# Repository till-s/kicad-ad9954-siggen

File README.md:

# Simple 1Hz-100MHz Signal Generator with AD9954

This project implements a simple sine-wave generator from a few Hz
to ~100MHz. The Reference/sampling frequency is 400MHz.
The output is buffered by a OP859 amplifier which does level-shifting,
and differential to single-ended conversion.

An analog LPF at the output supresses higher harmonics and provides
the DC-coupled signal into a 50 Ohm load (i.e., the filter was
designed for a 50Ohm termination). The ripple over the frequency range
is in the order of 1dB.

The output amplitude can be (digitally) scaled from ~1Vp (0.7V RMS) down
to 0Vp.

The AD9954 is programmed via USB (USB-SPI converter) by a simple python
software (in the sw/ subdirectory). Power is supplied by USB as well.

The assembled PCB fits into a Hammond 1455D601 extruded aluminum box
(60mm x 42.5mm x 23mm).

The PCB requires 4 layers.

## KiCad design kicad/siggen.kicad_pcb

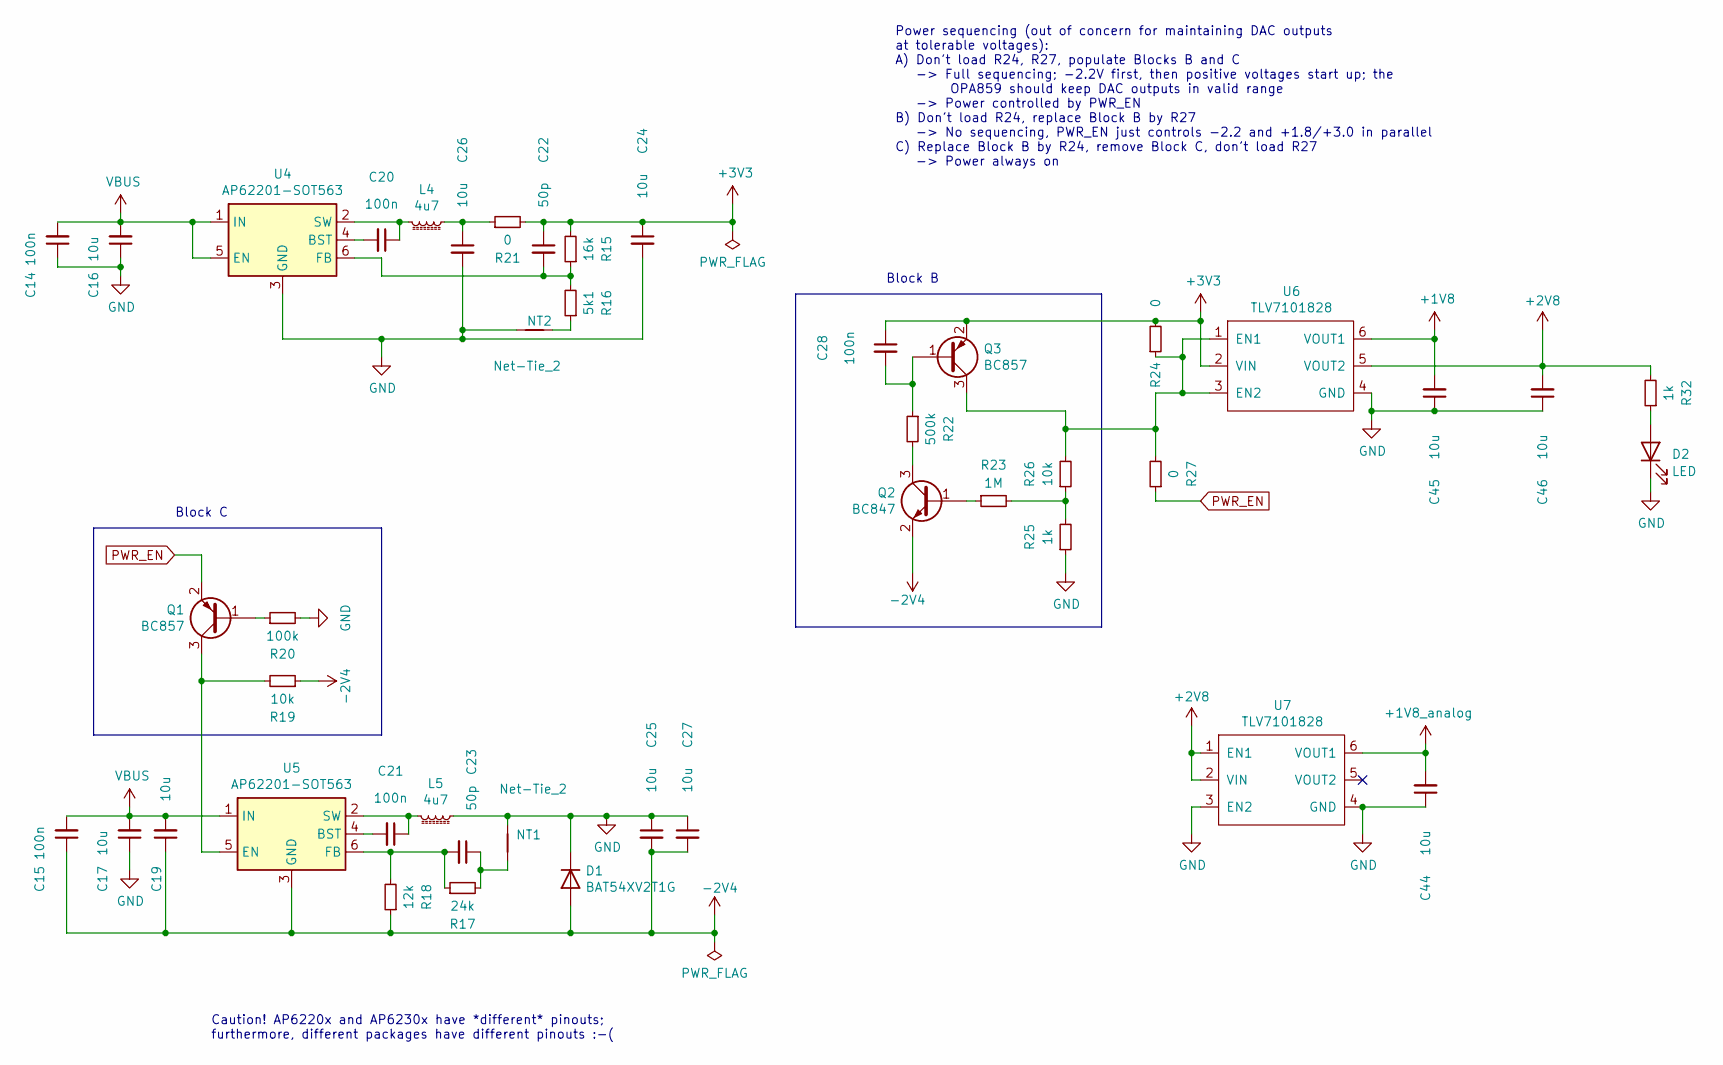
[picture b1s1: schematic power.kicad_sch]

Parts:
C14, C15, C20, C21, C28: 100n; C_0603_1608Metric
C16, C17, C19, C24, C25, C26, C27, C44, C45, C46: 10u; C_1206_3216Metric
C22, C23: 50p; C_0603_1608Metric
D1: BAT54XV2T1G; D_SOD-523
D2: LED; LED_0603_1608Metric
L4, L5: 4u7; L_Taiyo-Yuden_NR-50xx
NT1, NT2: Net-Tie_2; NetTie-2_SMD_Pad0.5mm
Q1, Q3: BC857; SOT-23
Q2: BC847; SOT-23
R15: 16k; R_0603_1608Metric
R16: 5k1; R_0603_1608Metric
R17: 24k; R_0603_1608Metric
R18: 12k; R_0603_1608Metric
R19, R26: 10k; R_0603_1608Metric
R20: 100k; R_0603_1608Metric
R21, R24, R27: 0; R_0603_1608Metric
R22: 500k; R_0603_1608Metric
R23: 1M; R_0603_1608Metric
R25, R32: 1k; R_0603_1608Metric
U4, U5: AP62201-SOT563; SOT-563-adjusted
U6, U7: TLV7101828; WSON-6_1.5x1.5mm_P0.5mm

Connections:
+1V8: C45.2, U6.6 (VOUT1); also elsewhere on the board
+1V8_analog: C44.2, U7.6 (VOUT1); also elsewhere on the board
+2V8: C46.2, R32.2, U6.5 (VOUT2), U7.1 (EN1), U7.2 (VIN); also elsewhere on the board
+3V3: C22.1, C24.1, C28.1, Q3.2 (E), R15.2, R21.2, R24.2, U6.2 (VIN); also elsewhere on the board
-2V4: C15.1, C19.1, C25.2, C27.2, D1.2 (A), Q2.2 (E), R18.1, R19.1, U5.3 (GND); also elsewhere on the board
GND: C14.1, C16.1, C17.1, C24.2, C25.1, C26.2, C27.1, C44.1, C45.1, C46.1, D1.1 (K), D2.1 (K), L5.1, NT1.1, NT2.2, R20.2, R25.1, U4.3 (GND), U6.4 (GND), U7.3 (EN2), U7.4 (GND); also elsewhere on the board
unnamed: C23.1, NT1.2, R17.2
unnamed: C26.1, L4.1, R21.1
unnamed: D2.2 (A), R32.1
unnamed: NT2.1, R16.1
unnamed: Q1.1 (B), R20.1
unnamed: Q1.3 (C), R19.2, U5.5 (EN)
unnamed: Q2.1 (B), R23.1
unnamed: Q2.3 (C), R22.2
unnamed: C28.2, Q3.1 (B), R22.1
unnamed: Q3.3 (C), R24.1, R26.2, R27.2, U6.1 (EN1), U6.3 (EN2)
unnamed: R23.2, R25.2, R26.1
unnamed: C20.2, U4.4 (BST)
unnamed: C22.2, R15.1, R16.2, U4.6 (FB)
unnamed: C20.1, L4.2, U4.2 (SW)
unnamed: C21.2, U5.4 (BST)
unnamed: C23.2, R17.1, R18.2, U5.6 (FB)
unnamed: C21.1, L5.2, U5.2 (SW)
PWR_EN: Q1.2 (E), R27.1; also elsewhere on the board
VBUS: C14.2, C15.2, C16.2, C17.2, C19.2, U4.1 (IN), U4.5 (EN), U5.1 (IN); also elsewhere on the board

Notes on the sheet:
Block B
Power sequencing (out of concern for maintaining DAC outputs at tolerable voltages): A) Don't load R24, R27, populate Blocks B and C -> Full sequencing; -2.2V first, then positive voltages start up; the OPA859 should keep DAC outputs in valid range -> Power controlled by PWR_EN B) Don't load R24, r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
Block C
Caution! AP6220x and AP6230x have *different* pinouts; furthermore, different packages have different pinouts :-(

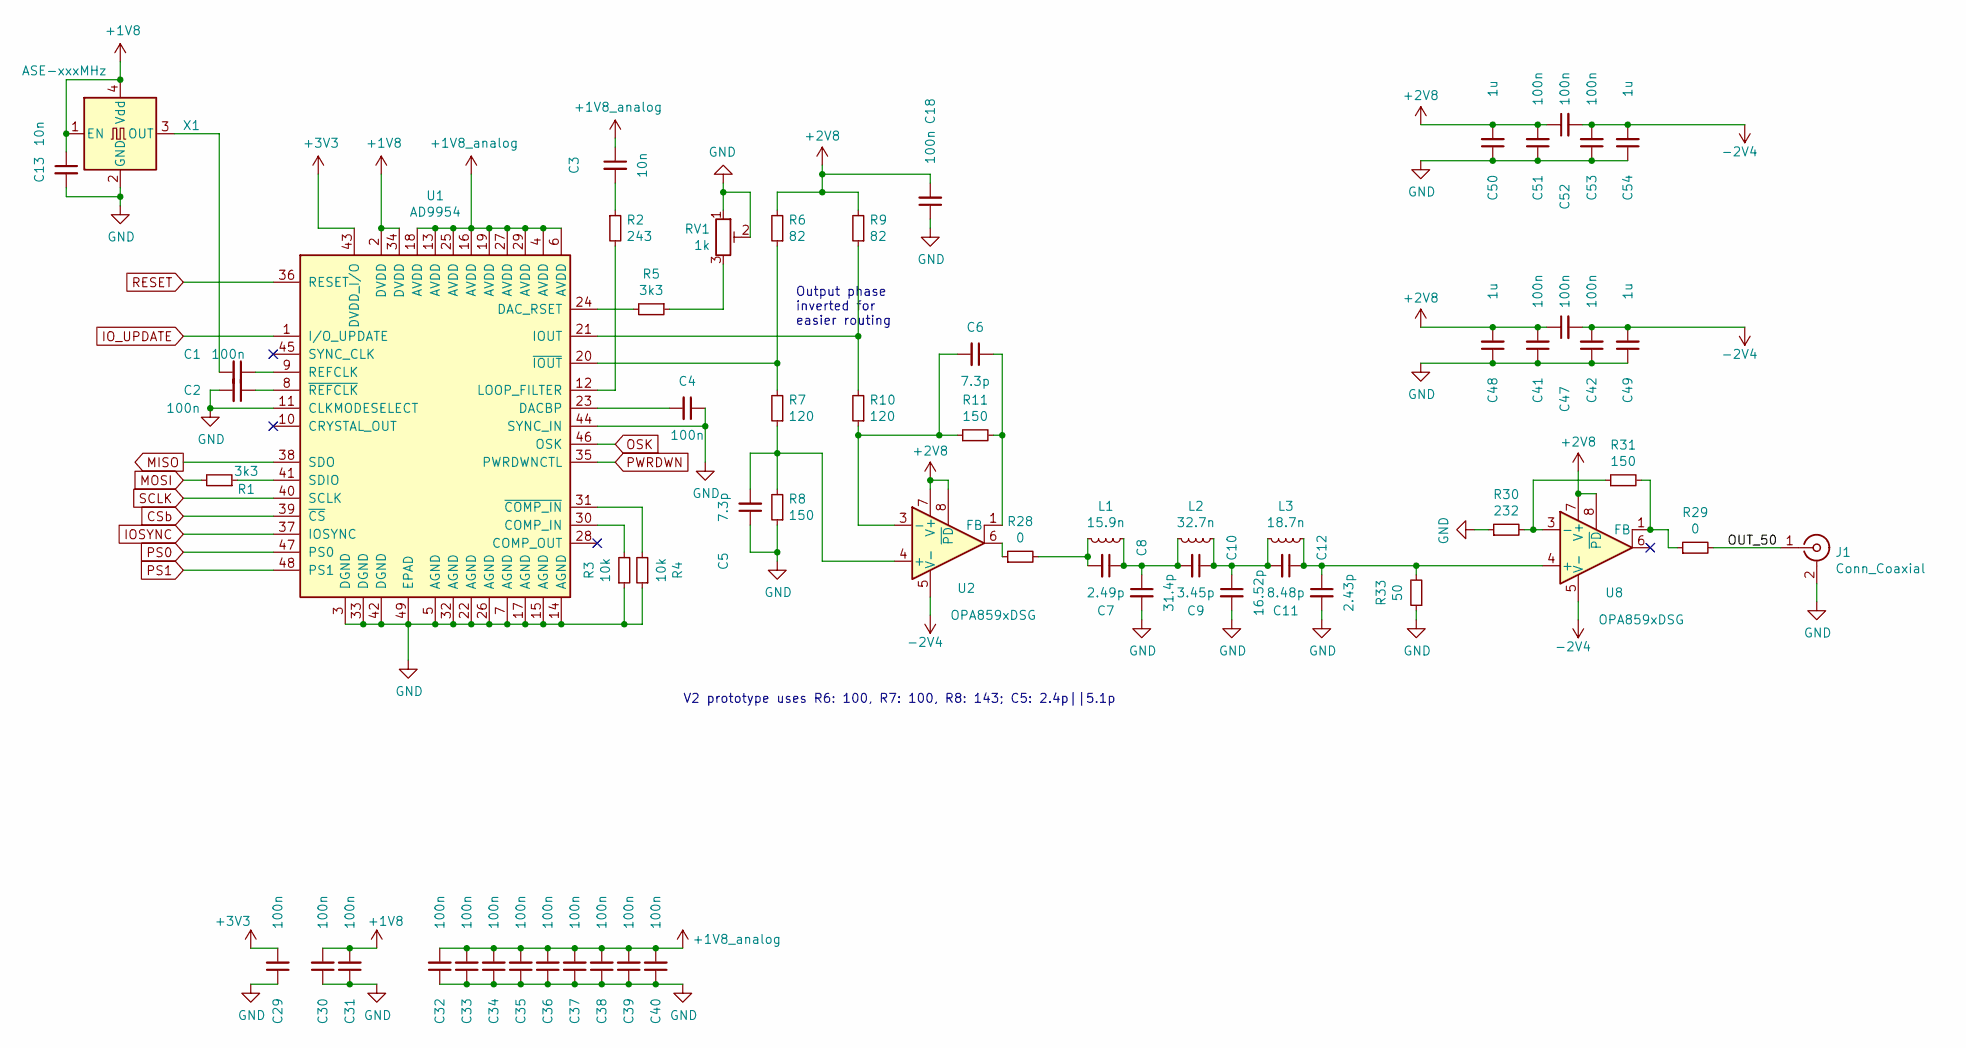
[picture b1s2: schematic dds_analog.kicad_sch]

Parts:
C1, C2: 100n; C_0603_1608Metric
C3, C13: 10n; C_0603_1608Metric
C4, C18, C29, C30, C31, C32, C33, C34, C35, C36, C37, C38, C39, C40, C41, C42, C47, C51, C52, C53: 100n; C_0402_1005Metric
C5, C6: 7.3p; C_0402_1005Metric
C7: 2.49p; C_0402_1005Metric
C8: 31.4p; C_0603_1608Metric
C9: 3.45p; C_0402_1005Metric
C10: 16.52p; C_0402_1005Metric
C11: 8.48p; C_0402_1005Metric
C12: 2.43p; C_0402_1005Metric
C48, C49, C50, C54: 1u; C_0805_2012Metric
J1: Conn_Coaxial; BNC_Molex_0731713150
L1: 15.9n; L_0603_1608Metric
L2: 32.7n; L_0603_1608Metric
L3: 18.7n; L_0603_1608Metric
R1, R5: 3k3; R_0603_1608Metric
R2: 243; R_0603_1608Metric
R3, R4: 10k; R_0603_1608Metric
R6, R9: 82; R_0402_1005Metric
R7, R10: 120; R_0402_1005Metric
R8, R11, R31: 150; R_0402_1005Metric
R28, R29: 0; R_0402_1005Metric
R30: 232; R_0402_1005Metric
R33: 50; R_0402_1005Metric
RV1: 1k; Bourns_PVG5A_Trimmer
U1: AD9954; TQFP-48-1EP_7x7mm_P0.5mm_EP3.5x3.5mm
U2, U8: OPA859xDSG; WSON-8-1EP_2x2mm_P0.5mm_EP0.9x1.6mm
X1: ASE-xxxMHz; Oscillator_SMD_Abracon_ASE-4Pin_3.2x2.5mm

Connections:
+1V8: C13.1, C30.2, C31.2, U1.2 (DVDD), U1.34 (DVDD), X1.1 (EN), X1.4 (Vdd); also elsewhere on the board
+1V8_analog: C3.1, C32.2, C33.2, C34.2, C35.2, C36.2, C37.2, C38.2, C39.2, C40.2, U1.4 (AVDD), U1.6 (AVDD), U1.13 (AVDD), U1.16 (AVDD), U1.18 (AVDD), U1.19 (AVDD), U1.25 (AVDD), U1.27 (AVDD), U1.29 (AVDD); also elsewhere on the board
+2V8: C18.2, C41.2, C47.1, C48.2, C50.2, C51.2, C52.1, R6.2, R9.2, U2.7 (V+), U2.8 (~PD), U8.7 (V+), U8.8 (~PD); also elsewhere on the board
+3V3: C29.2, U1.43 (DVDD_I/O); also elsewhere on the board
-2V4: C42.2, C47.2, C49.2, C52.2, C53.2, C54.2, U2.5 (V-), U2.9 (V-), U8.5 (V-), U8.9 (V-); also elsewhere on the board
/dds_analog/OUT_50: J1.1 (In), R29.2
CSb: U1.39 (~CS); also elsewhere on the board
GND: C2.2, C4.1, C5.1, C8.2, C10.2, C12.2, C13.2, C18.1, C29.1, C30.1, C31.1, C32.1, C33.1, C34.1, C35.1, C36.1, C37.1, C38.1, C39.1, C40.1, C41.1, C42.1, C48.1, C49.1, C50.1, C51.1, C53.1, C54.1, J1.2 (Ext), R3.1, R4.1, R8.1, R30.1, R33.1, RV1.1, RV1.2, U1.3 (DGND), U1.5 (AGND), U1.7 (AGND), U1.11 (CLKMODESELECT), U1.14 (AGND), U1.15 (AGND), U1.17 (AGND), U1.22 (AGND), U1.26 (AGND), U1.32 (AGND), U1.33 (DGND), U1.42 (DGND), U1.44 (SYNC_IN), U1.49 (EPAD), X1.2 (GND); also elsewhere on the board
IOSYNC: U1.37 (IOSYNC); also elsewhere on the board
IO_UPDATE: U1.1 (I/O_UPDATE); also elsewhere on the board
MISO: U1.38 (SDO); also elsewhere on the board
MOSI: R1.2; also elsewhere on the board
unnamed: C3.2, R2.1
unnamed: C7.1, C8.1, C9.2, L1.1, L2.2
unnamed: C7.2, L1.2, R28.2
unnamed: C9.1, C10.1, C11.2, L2.1, L3.2
unnamed: R5.1, RV1.3
unnamed: R28.1, U2.6
unnamed: R3.2, U1.30 (COMP_IN)
unnamed: C4.2, U1.23 (DACBP)
unnamed: R5.2, U1.24 (DAC_RSET)
unnamed: R9.1, R10.2, U1.21 (IOUT)
unnamed: R2.2, U1.12 (LOOP_FILTER)
unnamed: C1.1, U1.9 (REFCLK)
unnamed: R1.1, U1.41 (SDIO)
unnamed: R4.2, U1.31 (~COMP_IN)
unnamed: R6.1, R7.2, U1.20 (~IOUT)
unnamed: C2.1, U1.8 (~REFCLK)
unnamed: C5.2, R7.1, R8.2, U2.4 (+)
unnamed: C6.2, R10.1, R11.1, U2.3 (-)
unnamed: C6.1, R11.2, U2.1 (FB)
unnamed: C11.1, C12.1, L3.1, R33.2, U8.4 (+)
unnamed: R30.2, R31.1, U8.3 (-)
unnamed: R29.1, R31.2, U8.1 (FB)
unnamed: C1.2, X1.3 (OUT)
OSK: U1.46 (OSK); also elsewhere on the board
PS0: U1.47 (PS0); also elsewhere on the board
PS1: U1.48 (PS1); also elsewhere on the board
PWRDWN: U1.35 (PWRDWNCTL); also elsewhere on the board
RESET: U1.36 (RESET); also elsewhere on the board
SCLK: U1.40 (SCLK); also elsewhere on the board

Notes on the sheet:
V2 prototype uses R6: 100, R7: 100, R8: 143; C5: 2.4p||5.1p
Output phase inverted for easier routing

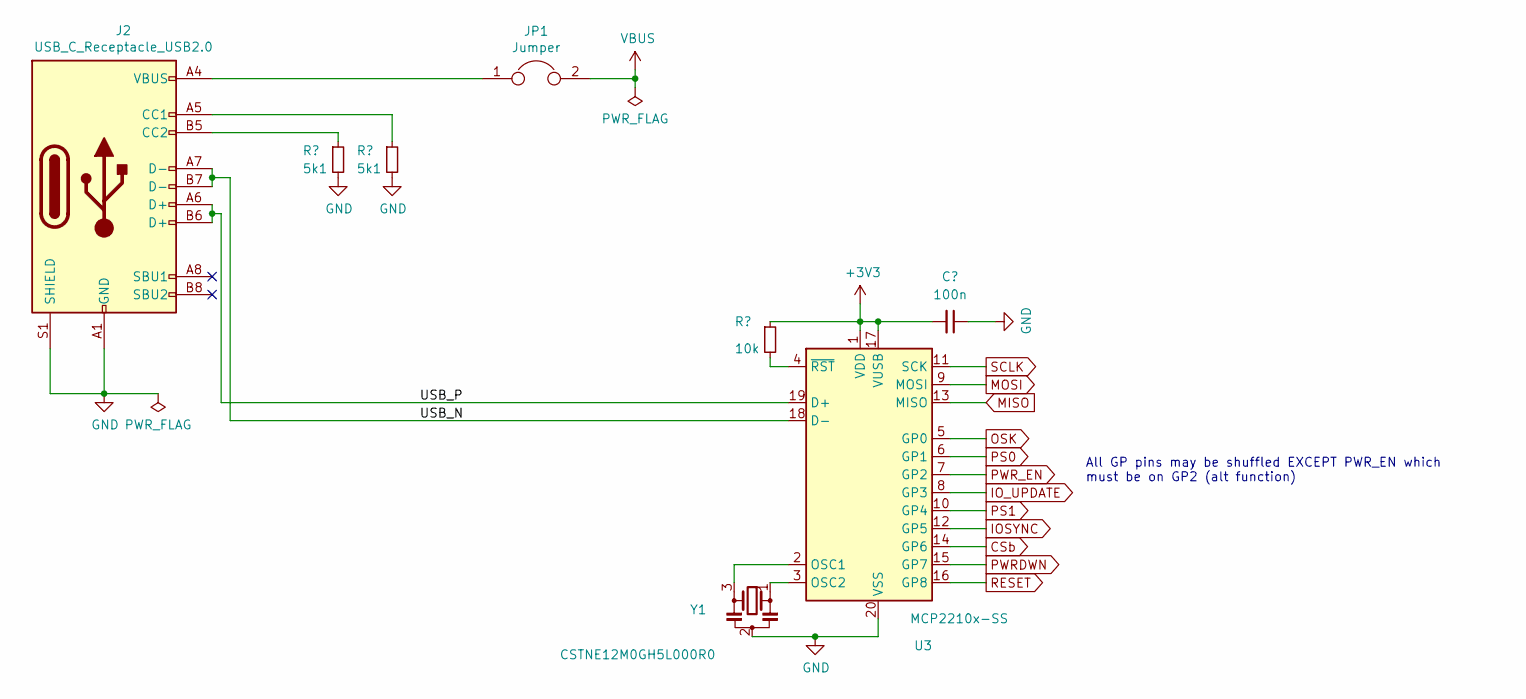
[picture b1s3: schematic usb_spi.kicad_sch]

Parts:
C43: 100n; C_0603_1608Metric
J2: USB_C_Receptacle_USB2.0; USB_C_Receptacle_Molex_2171790001_16P_TopMnt_Horizontal
JP1: Jumper; PinHeader_1x02_P1.27mm_Vertical_reduced_crtyd
R12, R13: 5k1; R_0603_1608Metric
R14: 10k; R_0603_1608Metric
U3: MCP2210x-SS; SSOP-20_5.3x7.2mm_P0.65mm
Y1: CSTNE12M0GH5L000R0; Resonator_SMD_muRata_CSTxExxV-3Pin_3.0x1.1mm

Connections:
+3V3: C43.2, R14.1, U3.1 (VDD), U3.17 (VUSB); also elsewhere on the board
/usb_spi/USB_N: J2.A7 (D-), J2.B7 (D-), U3.18 (D-)
/usb_spi/USB_P: J2.A6 (D+), J2.B6 (D+), U3.19 (D+)
CSb: U3.14 (GP6); also elsewhere on the board
GND: C43.1, J2.A1 (GND), J2.A12 (GND), J2.B1 (GND), J2.B12 (GND), J2.S1 (SHIELD), R12.2, R13.2, U3.20 (VSS), Y1.2; also elsewhere on the board
IOSYNC: U3.12 (GP5); also elsewhere on the board
IO_UPDATE: U3.8 (GP3); also elsewhere on the board
MISO: U3.13 (MISO); also elsewhere on the board
MOSI: U3.9 (MOSI); also elsewhere on the board
unnamed: J2.A5 (CC1), R13.1
unnamed: J2.B5 (CC2), R12.1
unnamed: J2.A4 (VBUS), J2.A9 (VBUS), J2.B4 (VBUS), J2.B9 (VBUS), JP1.1
unnamed: U3.2 (OSC1), Y1.3
unnamed: U3.3 (OSC2), Y1.1
unnamed: R14.2, U3.4 (~RST)
OSK: U3.5 (GP0); also elsewhere on the board
PS0: U3.6 (GP1); also elsewhere on the board
PS1: U3.10 (GP4); also elsewhere on the board
PWRDWN: U3.15 (GP7); also elsewhere on the board
PWR_EN: U3.7 (GP2); also elsewhere on the board
RESET: U3.16 (GP8); also elsewhere on the board
SCLK: U3.11 (SCK); also elsewhere on the board
VBUS: JP1.2; also elsewhere on the board

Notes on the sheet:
All GP pins may be shuffled EXCEPT PWR_EN which must be on GP2 (alt function)

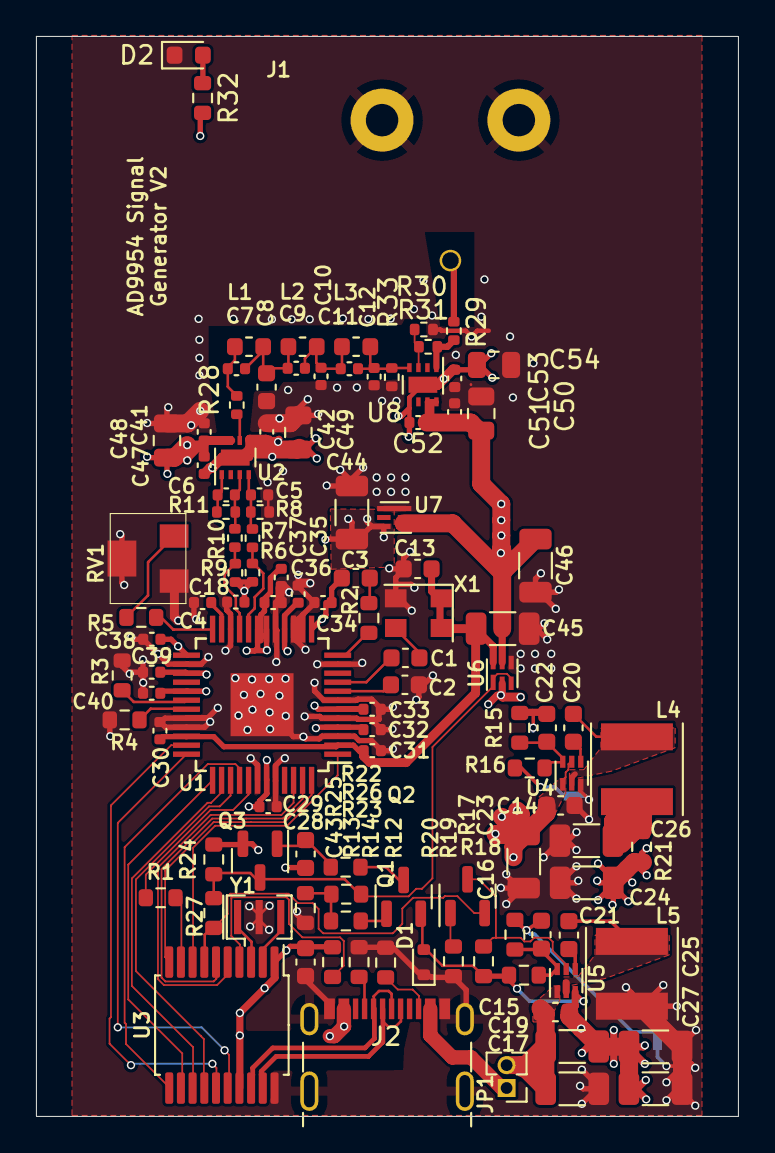
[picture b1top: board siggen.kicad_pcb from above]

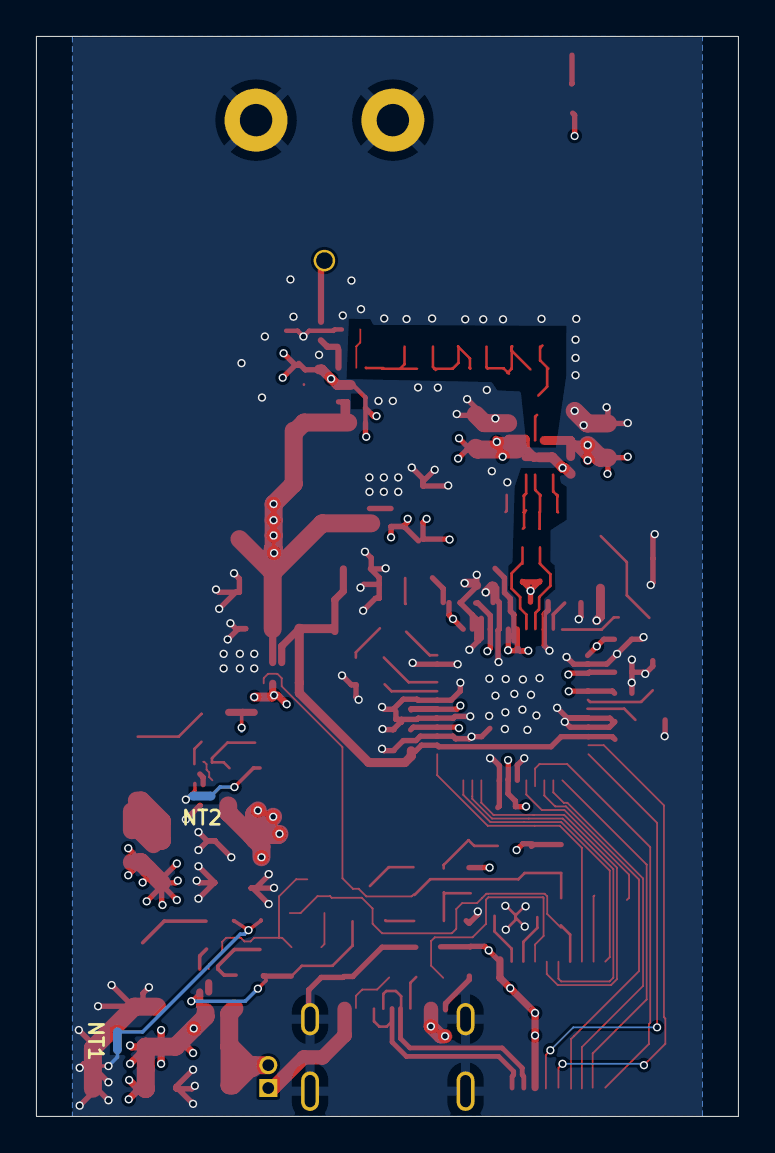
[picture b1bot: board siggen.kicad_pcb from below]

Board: 4 copper layers, 39.0 x 60.0 mm, 113 parts (2 on the bottom side), 68 nets.

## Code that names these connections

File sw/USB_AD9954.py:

#!/usr/bin/env python3
import hidapi

class SigGen(object):
  PIN_OSK       = 0
  PIN_PS0       = 1
  PIN_PWR_EN    = 2
  PIN_IO_UPDATE = 3

  PIN_PS1       = 4
  PIN_IOSYNC    = 5
  PIN_CSb       = 6
  PIN_PWRDWN    = 7
  # Reset / PIN8 is input only -> shorted to PIN_PWRDWN on V1 board
  # via solder bridge

  SPI_MODE = 0

  SPI_DIR_READ       = 0x80

  CMD_RD_GPIO_SETUP  = 0x20
  CMD_WR_GPIO_SETUP  = 0x21
  CMD_RD_GPIO_DIR    = 0x33
  CMD_WR_GPIO_DIR    = 0x32
  CMD_RD_GPIO_VALUE  = 0x31
  CMD_WR_GPIO_VALUE  = 0x30
  CMD_RD_SPI_SETUP   = 0x41
  CMD_WR_SPI_SETUP   = 0x40
  CMD_SPI_XFER       = 0x42
  CMD_SPI_CANCEL     = 0x11

  REG_CFR1           = 0x00
  CFR1_SDIO_IN       = (1<< 9)
  CFR1_OSK_EN        = (1<<25)
  CFR1_OSK_AUTO      = (1<<24)
  CFR1_CMP_PWRDWN    = (1<< 6)
  CFR1_SYNC_CLK_DIS  = (1<< 1)

  REG_CFR2           = 0x01
  CFR2_VCO_RNG_HI    = (1<< 2)
  CFR2_SHF_REF_MUL   = 3

  REG_ASF            = 0x02

  REG_FTW0           = 0x04

  REF_CLK_HZ         = 25.0e6

  def __init__(self, serial=None, dbg=False):
    self.dbg_       = dbg
    self.dev_       = hidapi.Device(vendor_id=0x4d8, product_id=0xde, serial_number=serial)
    self.rdGpio_    = bytearray(64)
    self.rdGpio_[0] = self.CMD_RD_GPIO_SETUP
    self.wrGpio_    = bytearray(64)
    self.wrGpio_[0] = self.CMD_WR_GPIO_VALUE
    rsp = self._io_(self.rdGpio_)
    if ( rsp[1] != 0 ):
      raise RuntimeError("Reading GPIO Status - error response")
    setGpio = bytearray(64)
    for i in range(64):
      setGpio[i] = rsp[i]
    setGpio[0] = self.CMD_WR_GPIO_SETUP
    setGpio[1] = 0
    setGpio[2] = 0
    setGpio[3] = 0
    for i in range(4, 4+9):
      setGpio[i] = 0   # GPIO
    setGpio[13] = 0x00 | (1<<self.PIN_PWR_EN) # all outputs zero, except PWR_EN
    setGpio[14] &= 0xfe
    setGpio[15] = 0x00 # all GPIO outputs
    setGpio[16] &= 0xfe
    self.wrGpio_[4] = setGpio[13]
    self._io_(setGpio, True)
    cmd = bytearray(64)
    cmd[0] = self.CMD_RD_SPI_SETUP
    rsp = self._io_(cmd)
    self.spiParms_ = bytearray(64)
    self.spiParms_[0] = self.CMD_WR_SPI_SETUP
    self.spiParms_[4:]= rsp[4:]
    self.spiParms_[20]= self.SPI_MODE
    self.sendSpiParms()
    cfr1  = self.CFR1_SDIO_IN
    cfr1 |= self.CFR1_OSK_EN 
    cfr1 |= self.CFR1_CMP_PWRDWN 
    cfr1 |= self.CFR1_SYNC_CLK_DIS
    self.regWrite(self.REG_CFR1, cfr1)
    self.setRefClk(400.0E6)

  def setRefClk(self, rate):
    m = int( round( rate/self.REF_CLK_HZ ) )
    if ( m > 20 ):
      raise RuntimeError("setRefClk() -- requested rate too high")
    if ( m < 4 ):
      m = 1
    self.sysClkHz_ = m * self.REF_CLK_HZ
    print("System Clock: {:g}".format(self.sysClkHz_))
    cfr2 = self.regRead( self.REG_CFR2 )
    cfr2 &= ~ 0xfc
    cfr2 |= (m << self.CFR2_SHF_REF_MUL)
    if ( self.sysClkHz_ > 250.0E6 ):
      cfr2 |= self.CFR2_VCO_RNG_HI
    self.regWrite( self.REG_CFR2, cfr2 )

  def setAmplitudeScale(self, scl):
    if ( scl < 0 or scl > 1.0 ):
      raise ValueError("SigGen.setAmplitudeScale() -- scale factor not in 0..1")
    v = self.regRead( self.REG_ASF )
    v &= ~0x3fff
    v |= int(0x3fff*scl)
    self.regWrite( self.REG_ASF, v)

  def getAmplitudeScale(self):
    v = self.regRead( self.REG_ASF )
    return float(v & 0x3fff)/0x3fff

  def setFrequencyHz(self, f, ftw1 = False):
    ftw = int(round(f/self.sysClkHz_ * 2.0**32))
    if ( ftw < 0 or ftw > 2**31 ):
      raise ValueError("SigGen.setFrequency() -- value out of range")
    if ftw1:
      reg = self.REG_FTW1
    else:
      reg = self.REG_FTW0
    self.regWrite(reg, ftw)

  def getFrequencyHz(self, ftw1 = False):
    if ftw1:
      reg = self.REG_FTW1
    else:
      reg = self.REG_FTW0
    v = self.regRead( reg )
    return v/2.0**32 * self.sysClkHz_

  def _io_(self, buf, check1 = False):
    self.dev_.write(buf)
    rsp = self.dev_.read(64)
    if ( check1 and ( rsp[1] != 0 ) ):
      raise RuntimeError("IO Error response {:d}".format(rsp[1]))
    return rsp

  def sendSpiParms(self):
    rsp = self._io_(self.spiParms_)
    if ( rsp[1] != 0 ):
      raise RuntimeError("Setting SPI parameters failed")

  def flashGpio(self, n):
    self.setGpio( n, 1 )
    self.setGpio( n, 0 )

  def ioSync(self):
    self.flashGpio( self.PIN_IOSYNC )

  def ioUpdate(self):
    self.flashGpio( self.PIN_IO_UPDATE )

  def setGpio(self, n, val):
    if ( n < 0 or n > 8 ):
      raise RuntimeError("Invalid GPIO pin")
    i   = 4 + int(n / 8)
    n   = n % 8
    if ( val != 0 ):
      self.wrGpio_[i] |=  (1<<n)
    else:
      self.wrGpio_[i] &= ~(1<<n)
    self._io_(self.wrGpio_, True)

  def getGpios(self):
    d = bytearray(64)
    d[0] = self.CMD_RD_GPIO_VALUE
    rsp = self._io_(d, True)
    return rsp[4] | ((rsp[5] & 1) << 8)

  def powerOn(self):
    self.setGpio(2, 1)

  def powerOff(self):
    self.setGpio(2, 0)

  def spi(self, buf = bytearray(0)):
    if (type(buf) != bytearray) or (len(buf) > 60):
      raise RuntimeError("SigGen.spi: invalid data")
    snd = bytearray(64)
    snd[0] = self.CMD_SPI_XFER
    snd[1] = len(buf)
    snd[4:4+len(buf)] = buf
    if ( len(buf) > 0 ):
      if ( ((self.spiParms_[19] << 8) | self.spiParms_[18]) != len(buf) ):
        self.spiParms_[19] = 0
        self.spiParms_[18] = len(buf)
        self.sendSpiParms()
    rsp = self._io_(snd)
    if   ( rsp[1] == 0xf7 ):
      raise RuntimeError("SPI: bus not available")
    elif ( rsp[1] == 0x00 ):
      got = rsp[2]
      if (self.dbg_):
        print("SPI status 0x{:x}, got {:d}".format(rsp[3], got))
      return rsp[4:4+got]
    elif ( rsp[1] == 0xf8 ):
      raise RuntimeError("SPI: xfer in progress")
    else:
      raise RuntimeError("SPI: Unexpected response")

  def spiCancel(self):
    snd = bytearray(64)
    snd[0] = self.CMD_SPI_CANCEL
    rsp = self._io_(snd)
    print("SPI cancel: no ext req: {:d}, owner {:d}".format( rsp[2], rsp[3]))

  def regLen(self, ri):
    ll = [4, 3, 2, 1, 4, 2, 5, 5, 5, 5]
    if ( ri < 0 or ri >= len(ll) ):
      raise RuntimeError("SigGen.regLen() - invalid register index")
    return ll[ri]

  def regWrite(self, ri, val):
    d = bytearray(self.regLen(ri) + 1)
    for i in range(-1, -len(d), -1):
      d[i]  = val % 256
      val >>= 8
    d[0] = ri
    self.spi( d )
    self.spi()
    self.ioUpdate()
    
  def regRead(self, ri):
    d = bytearray(self.regLen(ri) + 1)
    d[0] = ri | self.SPI_DIR_READ
    self.spi( d )
    v = 0
    for x in self.spi()[1:]:
      v = (v<<8) | x
    return v
 
#sg=SigGen()
# usage example:
# sg.setFrequencyHz(1.3E6)
# scale between 0..1
# sg.setAmplitudeScale(0.2)

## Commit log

2022-10-11 initial import
2022-10-11 added pcb file
2022-10-11 updated errata
2022-10-11 README.md: added
2022-10-11 removed frontent/amp test circuit
    This circuit had shared the PCB for cost reasons.
2022-10-11 moved RV1 (pot) away from board edge (README.errata)
2022-10-11 USB_AD9954.py: added support for GP8 and 'getGpios()'
2022-10-11 renamed (removed 'v1' in filenames)
2022-10-11 renamed objects that had '-v1' in their names
2022-10-17 updated README.errata (recommend adding output stage)
2023-11-01 Added output buffer; power LED
2023-11-01 prepare for jlcpcb order (v2)
2023-12-01 modified a few values (as loaded on v2 prototype board)
2023-12-01 emphasize that the values are for the V2 *prototype*
    The final version uses different voltages: 2.8/-2.4 (vs 3.0/-2.2).
2023-12-01 changed values in schematic for v2 board
    Most notably: moved from +3.0/-2.2V to +2.8/-2.4V analog supply.
    This required changing the diff-amp resistors to stay within
    the common-mode range of the AD9954 and the OPA859.
